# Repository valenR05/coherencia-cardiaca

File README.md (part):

<?xml version="1.0" encoding="utf-8"?>
<!DOCTYPE eagle SYSTEM "eagle.dtd">
<eagle version="9.6.2">
<drawing>
<settings>
<setting alwaysvectorfont="no"/>
<setting verticaltext="up"/>
</settings>
<grid distance="0.1" unitdist="inch" unit="inch" style="lines" multiple="1" display="no" altdistance="0.01" altunitdist="inch" altunit="inch"/>
<layers>
<layer number="1" name="Top" color="4" fill="1" visible="no" active="no"/>
<layer number="2" name="Route2" color="16" fill="1" visible="no" active="no"/>
<layer number="3" name="Route3" color="17" fill="1" visible="no" active="no"/>
<layer number="4" name="Route4" color="18" fill="1" visible="no" active="no"/>
<layer number="5" name="Route5" color="19" fill="1" visible="no" active="no"/>
<layer number="6" name="Route6" color="25" fill="1" visible="no" active="no"/>
<layer number="7" name="Route7" color="26" fill="1" visible="no" active="no"/>
<layer number="8" name="Route8" color="27" fill="1" visible="no" active="no"/>
<layer number="9" name="Route9" color="28" fill="1" visible="no" active="no"/>
<layer number="10" name="Route10" color="29" fill="1" visible="no" active="no"/>
<layer number="11" name="Route11" color="30" fill="1" visible="no" active="no"/>
<layer number="12" name="Route12" color="20" fill="1" visible="no" active="no"/>
<layer number="13" name="Route13" color="21" fill="1" visible="no" active="no"/>
<layer number="14" name="Route14" color="22" fill="1" visible="no" active="no"/>
<layer number="15" name="Route15" color="23" fill="1" visible="no" active="no"/>
<layer number="16" name="Bottom" color="1" fill="1" visible="no" active="no"/>
<layer number="17" name="Pads" color="2" fill="1" visible="no" active="no"/>
<layer number="18" name="Vias" color="2" fill="1" visible="no" active="no"/>
<layer number="19" name="Unrouted" color="6" fill="1" visible="no" active="no"/>
<layer number="20" name="Dimension" color="15" fill="1" visible="no" active="no"/>
<layer number="21" name="tPlace" color="7" fill="1" visible="no" active="no"/>
<layer number="22" name="bPlace" color="7" fill="1" visible="no" active="no"/>
<layer number="23" name="tOrigins" color="15" fill="1" visible="no" active="no"/>
<layer number="24" name="bOrigins" color="15" fill="1" visible="no" active="no"/>
<layer number="25" name="tNames" color="7" fill="1" visible="no" active="no"/>
<layer number="26" name="bNames" color="7" fill="1" visible="no" active="no"/>
<layer number="27" name="tValues" color="7" fill="1" visible="no" active="no"/>
<layer number="28" name="bValues" color="7" fill="1" visible="no" active="no"/>
<layer number="29" name="tStop" color="7" fill="3" visible="no" active="no"/>
<layer number="30" name="bStop" color="7" fill="6" visible="no" active="no"/>
<layer number="31" name="tCream" color="7" fill="4" visible="no" active="no"/>
<layer number="32" name="bCream" color="7" fill="5" visible="no" active="no"/>
<layer number="33" name="tFinish" color="6" fill="3" visible="no" active="no"/>
<layer number="34" name="bFinish" color="6" fill="6" visible="no" active="no"/>
<layer number="35" name="tGlue" color="7" fill="4" visible="no" active="no"/>
<layer number="36" name="bGlue" color="7" fill="5" visible="no" active="no"/>
<layer number="37" name="tTest" color="7" fill="1" visible="no" active="no"/>
<layer number="38" name="bTest" color="7" fill="1" visible="no" active="no"/>
<layer number="39" name="tKeepout" color="4" fill="11" visible="no" active="no"/>
<layer number="40" name="bKeepout" color="1" fill="11" visible="no" active="no"/>
<layer number="41" name="tRestrict" color="4" fill="10" visible="no" active="no"/>
<layer number="42" name="bRestrict" color="1" fill="10" visible="no" active="no"/>
<layer number="43" name="vRestrict" color="2" fill="10" visible="no" active="no"/>
<layer number="44" name="Drills" color="7" fill="1" visible="no" active="no"/>
<layer number="45" name="Holes" color="7" fill="1" visible="no" active="no"/>
<layer number="46" name="Milling" color="3" fill="1" visible="no" active="no"/>
<layer number="47" name="Measures" color="7" fill="1" visible="no" active="no"/>
<layer number="48" name="Document" color="7" fill="1" visible="no" active="no"/>
<layer number="49" name="Reference" color="7" fill="1" visible="no" active="no"/>
<layer number="50" name="dxf" color="7" fill="1" visible="no" active="no"/>
<layer number="51" name="tDocu" color="7" fill="1" visible="no" active="no"/>
<layer number="52" name="bDocu" color="7" fill="1" visible="no" active="no"/>
<layer number="53" name="tGND_GNDA" color="7" fill="9" visible="no" active="no"/>
<layer number="54" name="bGND_GNDA" color="1" fill="9" visible="no" active="no"/>
<layer number="56" name="wert" color="7" fill="1" visible="no" active="no"/>
<layer number="57" name="tCAD" color="7" fill="1" visible="no" active="no"/>
<layer number="59" name="tCarbon" color="7" fill="1" visible="no" active="no"/>
<layer number="60" name="bCarbon" color="7" fill="1" visible="no" active="no"/>
<layer number="88" name="SimResults" color="9" fill="1" visible="yes" active="yes"/>
<layer number="89" name="SimProbes" color="9" fill="1" visible="yes" active="yes"/>
<layer number="90" name="Modules" color="5" fill="1" visible="yes" active="yes"/>
<layer number="91" name="Nets" color="2" fill="1" visible="yes" active="yes"/>
<layer number="92" name="Busses" color="1" fill="1" visible="yes" active="yes"/>
<layer number="93" name="Pins" color="2" fill="1" visible="no" active="yes"/>
<layer number="94" name="Symbols" color="4" fill="1" visible="yes" active="yes"/>
<layer number="95" name="Names" color="7" fill="1" visible="yes" active="yes"/>
<layer number="96" name="Values" color="7" fill="1" visible="yes" active="yes"/>
<layer number="97" name="Info" color="7" fill="1" visible="yes" active="yes"/>
<layer number="98" name="Guide" color="6" fill="1" visible="yes" active="yes"/>
<layer number="99" name="SpiceOrder" color="7" fill="1" visible="no" active="no"/>
<layer number="100" name="Muster" color="7" fill="1" visible="no" active="no"/>
<layer number="101" name="Patch_Top" color="12" fill="4" visible="no" active="yes"/>
<layer number="102" name="Vscore" color="7" fill="1" visible="no" active="yes"/>
<layer number="103" name="fp3" color="7" fill="1" visible="no" active="yes"/>
<layer number="104" name="Name" color="7" fill="1" visible="no" active="yes"/>
<layer number="105" name="Beschreib" color="9" fill="1" visible="no" active="yes"/>
<layer number="106" name="BGA-Top" color="4" fill="1" visible="no" active="yes"/>
<layer number="107" name="BD-Top" color="5" fill="1" visible="no" active="yes"/>
<layer number="108" name="fp8" color="7" fill="1" visible="no" active="yes"/>
<layer number="109" name="fp9" color="7" fill="1" visible="no" active="yes"/>
<layer number="110" name="fp0" color="7" fill="1" visible="no" active="yes"/>
<layer number="111" name="LPC17xx" color="7" fill="1" visible="no" active="yes"/>
<layer number="112" name="tSilk" color="7" fill="1" visible="no" active="yes"/>
<layer number="113" name="ReferenceLS" color="7" fill="1" visible="no" active="no"/>
<layer number="116" name="Patch_BOT" color="9" fill="4" visible="no" active="yes"/>
<layer number="118" name="Rect_Pads" color="7" fill="1" visible="no" active="no"/>
<layer number="121" name="_tsilk" color="7" fill="1" visible="no" active="yes"/>
<layer number="122" name="_bsilk" color="7" fill="1" visible="no" active="yes"/>
<layer number="123" name="tTestmark" color="7" fill="1" visible="no" active="yes"/>
<layer number="124" name="bTestmark" color="7" fill="1" visible="no" active="yes"/>
<layer number="125" name="_tNames" color="7" fill="1" visible="no" active="yes"/>
<layer number="126" name="_bNames" color="7" fill="1" visible="no" active="yes"/>
<layer number="127" name="_tValues" color="7" fill="1" visible="no" active="yes"/>
<layer number="128" name="_bValues" color="7" fill="1" visible="no" active="yes"/>
<layer number="129" name="Mask" color="7" fill="1" visible="yes" active="yes"/>
<layer number="131" name="tAdjust" color="7" fill="1" visible="no" active="yes"/>
<layer number="132" name="bAdjust" color="7" fill="1" visible="no" active="yes"/>
<layer number="144" name="Drill_legend" color="7" fill="1" visible="no" active="yes"/>
<layer number="150" name="Notes" color="7" fill="1" visible="no" active="yes"/>
<layer number="151" name="HeatSink" color="7" fill="1" visible="no" active="yes"/>
<layer number="152" name="_bDocu" color="7" fill="1" visible="no" active="yes"/>
<layer number="153" name="FabDoc1" color="6" fill="1" visible="no" active="no"/>
<layer number="154" name="FabDoc2" color="2" fill="1" visible="no" active="no"/>
<layer number="155" name="FabDoc3" color="7" fill="15" visible="no" active="no"/>
<layer number="199" name="Contour" color="7" fill="1" visible="no" active="yes"/>
<layer number="200" name="200bmp" color="1" fill="10" visible="no" active="yes"/>
<layer number="201" name="201bmp" color="2" fill="1" visible="no" active="no"/>
<layer number="202" name="202bmp" color="3" fill="1" visible="no" active="no"/>
<layer number="203" name="203bmp" color="4" fill="10" visible="no" active="yes"/>
<layer number="204" name="204bmp" color="5" fill="10" visible="no" active="yes"/>
<layer number="205" name="205bmp" color="6" fill="10" visible="no" active="yes"/>
<layer number="206" name="206bmp" color="7" fill="10" visible="no" active="yes"/>
<layer number="207" name="207bmp" color="8" fill="10" visible="no" active="yes"/>
<layer number="208" name="208bmp" color="9" fill="10" visible="no" active="yes"/>
<layer number="209" name="209bmp" color="7" fill="1" visible="no" active="yes"/>
<layer number="210" name="210bmp" color="7" fill="1" visible="no" active="yes"/>
<layer number="211" name="211bmp" color="7" fill="1" visible="no" active="yes"/>
<layer number="212" name="212bmp" color="7" fill="1" visible="no" active="yes"/>
<layer number="213" name="213bmp" color="7" fill="1" visible="no" active="yes"/>
<layer number="214" name="214bmp" color="7" fill="1" visible="no" active="yes"/>
<layer number="215" name="215bmp" color="7" fill="1" visible="no" active="yes"/>
<layer number="216" name="216bmp" color="7" fill="1" visible="no" active="yes"/>
<layer number="217" name="217bmp" color="18" fill="1" visible="no" active="no"/>
<layer number="218" name="218bmp" color="19" fill="1" visible="no" active="no"/>
<layer number="219" name="219bmp" color="20" fill="1" visible="no" active="no"/>
<layer number="220" name="220bmp" color="21" fill="1" visible="no" active="no"/>
<layer number="221" name="221bmp" color="22" fill="1" visible="no" active="no"/>
<layer number="222" name="222bmp" color="23" fill="1" visible="no" active="no"/>
<layer number="223" name="223bmp" color="24" fill="1" visible="no" active="no"/>
<layer number="224" name="224bmp" color="25" fill="1" visible="no" active="no"/>
<layer number="225" name="225bmp" color="7" fill="1" visible="yes" active="yes"/>
<layer number="226" name="226bmp" color="7" fill="1" visible="yes" active="yes"/>
<layer number="227" name="227bmp" color="7" fill="1" visible="yes" active="yes"/>
<layer number="228" name="228bmp" color="7" fill="1" visible="yes" active="yes"/>
<layer number="229" name="229bmp" color="7" fill="1" visible="yes" active="yes"/>
<layer number="230" name="230bmp" color="7" fill="1" visible="yes" active="yes"/>
<layer number="231" name="Eagle3D_PG1" color="7" fill="1" visible="no" active="no"/>
<layer number="232" name="Eagle3D_PG2" color="7" fill="1" visible="no" active="no"/>
<layer number="233" name="Eagle3D_PG3" color="7" fill="1" visible="no" active="no"/>
<layer number="248" name="Housing" color="7" fill="1" visible="no" active="yes"/>
<layer number="249" name="Edge" color="7" fill="1" visible="no" active="yes"/>
<layer number="250" name="Descript" color="7" fill="1" visible="no" active="no"/>
<layer number="251" name="SMDround" color="7" fill="1" visible="no" active="no"/>
<layer number="254" name="cooling" color="7" fill="1" visible="no" active="yes"/>
<layer number="255" name="routoute" color="7" fill="1" visible="yes" active="yes"/>
</layers>
<schematic xreflabel="%F%N/%S.%C%R" xrefpart="/%S.%C%R">
<libraries>
<library name="TS321IDBVR">
<description>&lt;Texas Instruments TS321IDBVR Op Amp, 0.8MHz, 5  32 V, 5-Pin SOT-23&lt;/b&gt;&lt;p&gt;
&lt;author&gt;Created by SamacSys&lt;/author&gt;</description>
<packages>
<package name="SOT95P280X145-5N">
<description>&lt;b&gt;DBV0005A&lt;/b&gt;&lt;br&gt;
</description>
<smd name="1" x="-1.25" y="0.95" dx="1.2" dy="0.6" layer="1"/>
<smd name="2" x="-1.25" y="0" dx="1.2" dy="0.6" layer="1"/>
<smd name="3" x="-1.25" y="-0.95" dx="1.2" dy="0.6" layer="1"/>
<smd name="4" x="1.25" y="-0.95" dx="1.2" dy="0.6" layer="1"/>
<smd name="5" x="1.25" y="0.95" dx="1.2" dy="0.6" layer="1"/>
<text x="0" y="0" size="1.27" layer="25" align="center">&gt;NAME</text>
<text x="0" y="0" size="1.27" layer="27" align="center">&gt;VALUE</text>
<wire x1="-2.1" y1="1.775" x2="2.1" y2="1.775" width="0.05" layer="51"/>
<wire x1="2.1" y1="1.775" x2="2.1" y2="-1.775" width="0.05" layer="51"/>
<wire x1="2.1" y1="-1.775" x2="-2.1" y2="-1.775" width="0.05" layer="51"/>
<wire x1="-2.1" y1="-1.775" x2="-2.1" y2="1.775" width="0.05" layer="51"/>
<wire x1="-0.8" y1="1.45" x2="0.8" y2="1.45" width="0.1" layer="51"/>
<wire x1="0.8" y1="1.45" x2="0.8" y2="-1.45" width="0.1" layer="51"/>
<wire x1="0.8" y1="-1.45" x2="-0.8" y2="-1.45" width="0.1" layer="51"/>
<wire x1="-0.8" y1="-1.45" x2="-0.8" y2="1.45" width="0.1" layer="51"/>
<wire x1="-0.8" y1="0.5" x2="0.15" y2="1.45" width="0.1" layer="51"/>
<wire x1="-0.3" y1="1.45" x2="0.3" y2="1.45" width="0.2" layer="21"/>
<wire x1="0.3" y1="1.45" x2="0.3" y2="-1.45" width="0.2" layer="21"/>
<wire x1="0.3" y1="-1.45" x2="-0.3" y2="-1.45" width="0.2" layer="21"/>
<wire x1="-0.3" y1="-1.45" x2="-0.3" y2="1.45" width="0.2" layer="21"/>
<wire x1="-1.85" y1="1.5" x2="-0.65" y2="1.5" width="0.2" layer="21"/>
</package>
</packages>
<symbols>
<symbol name="TS321IDBVR">
<wire x1="5.08" y1="2.54" x2="22.86" y2="2.54" width="0.254" layer="94"/>
<wire x1="22.86" y1="-7.62" x2="22.86" y2="2.54" width="0.254" layer="94"/>
<wire x1="22.86" y1="-7.62" x2="5.08" y2="-7.62" width="0.254" layer="94"/>
<wire x1="5.08" y1="2.54" x2="5.08" y2="-7.62" width="0.254" layer="94"/>
<text x="24.13" y="7.62" size="1.778" layer="95" align="center-left">&gt;NAME</text>
<text x="24.13" y="5.08" size="1.778" layer="96" align="center-left">&gt;VALUE</text>
<pin name="OUT" x="0" y="0" length="middle"/>
<pin name="VCC" x="0" y="-2.54" length="middle"/>
<pin name="IN+" x="0" y="-5.08" length="middle"/>
<pin name="IN-" x="27.94" y="0" length="middle" rot="R180"/>
<pin name="VCC+" x="27.94" y="-2.54" length="middle" rot="R180"/>
</symbol>
</symbols>
<devicesets>
<deviceset name="TS321IDBVR" prefix="IC">
<description>&lt;b&gt;Texas Instruments TS321IDBVR Op Amp, 0.8MHz, 5  32 V, 5-Pin SOT-23&lt;/b&gt;&lt;p&gt;
Source: &lt;a href="http://www.ti.com/lit/gpn/ts321"&gt; Datasheet &lt;/a&gt;</description>
<gates>
<gate name="G$1" symbol="TS321IDBVR" x="0" y="0"/>
</gates>
<devices>
<device name="" package="SOT95P280X145-5N">
<connects>
<connect gate="G$1" pin="IN+" pad="3"/>
<connect gate="G$1" pin="IN-" pad="4"/>
<connect gate="G$1" pin="OUT" pad="1"/>
<connect gate="G$1" pin="VCC" pad="2"/>
<connect gate="G$1" pin="VCC+" pad="5"/>
</connects>
<technologies>
<technology name="">
<attribute name="DESCRIPTION" value="Texas Instruments TS321IDBVR Op Amp, 0.8MHz, 5  32 V, 5-Pin SOT-23" constant="no"/>
<attribute name="HEIGHT" value="1.45mm" constant="no"/>
<attribute name="MANUFACTURER_NAME" value="Texas Instruments" constant="no"/>
<attribute name="MANUFACTURER_PART_NUMBER" value="TS321IDBVR" constant="no"/>
<attribute name="MOUSER_PART_NUMBER" value="595-TS321IDBVR" constant="no"/>
<attribute name="MOUSER_PRICE-STOCK" value="https://www.mouser.co.uk/ProductDetail/Texas-Instruments/TS321IDBVR?qs=BBezV1N05%2FuyNsgiemJ6Dw%3D%3D" constant="no"/>
</technology>
</technologies>
</device>
</devices>
</deviceset>
</devicesets>
</library>
<library name="ESP32-S3-WROOM-1-N16R8">
<description>&lt;Multiprotocol Modules SMD Module, ESP32-S3R8, 3.3V, 8 MB Octal PSRAM Die, 16 MB Quad SPI Flash, PCB Antenna&lt;/b&gt;&lt;p&gt;
&lt;author&gt;Created by SamacSys&lt;/author&gt;</description>
<packages>
<package name="ESP32S3WROOM1N16R8">
<description>&lt;b&gt;ESP32-S3-WROOM-1-N16R8-5&lt;/b&gt;&lt;br&gt;
</description>
<smd name="1" x="-8.75" y="5.26" dx="1.5" dy="0.9" layer="1"/>
<smd name="2" x="-8.75" y="3.99" dx="1.5" dy="0.9" layer="1"/>
<smd name="3" x="-8.75" y="2.72" dx="1.5" dy="0.9" layer="1"/>
<smd name="4" x="-8.75" y="1.45" dx="1.5" dy="0.9" layer="1"/>
<smd name="5" x="-8.75" y="0.18" dx="1.5" dy="0.9" layer="1"/>
<smd name="6" x="-8.75" y="-1.09" dx="1.5" dy="0.9" layer="1"/>
<smd name="7" x="-8.75" y="-2.36" dx="1.5" dy="0.9" layer="1"/>
<smd name="8" x="-8.75" y="-3.63" dx="1.5" dy="0.9" layer="1"/>
<smd name="9" x="-8.75" y="-4.9" dx="1.5" dy="0.9" layer="1"/>
<smd name="10" x="-8.75" y="-6.17" dx="1.5" dy="0.9" layer="1"/>
<smd name="11" x="-8.75" y="-7.44" dx="1.5" dy="0.9" layer="1"/>
<smd name="12" x="-8.75" y="-8.71" dx="1.5" dy="0.9" layer="1"/>
<smd name="13" x="-8.75" y="-9.98" dx="1.5" dy="0.9" layer="1"/>
<smd name="14" x="-8.75" y="-11.25" dx="1.5" dy="0.9" layer="1"/>
<smd name="15" x="-6.985" y="-12.5" dx="1.5" dy="0.9" layer="1" rot="R90"/>
<smd name="16" x="-5.715" y="-12.5" dx="1.5" dy="0.9" layer="1" rot="R90"/>
<smd name="17" x="-4.445" y="-12.5" dx="1.5" dy="0.9" layer="1" rot="R90"/>
<smd name="18" x="-3.175" y="-12.5" dx="1.5" dy="0.9" layer="1" rot="R90"/>
<smd name="19" x="-1.905" y="-12.5" dx="1.5" dy="0.9" layer="1" rot="R90"/>
<smd name="20" x="-0.635" y="-12.5" dx="1.5" dy="0.9" layer="1" rot="R90"/>
<smd name="21" x="0.635" y="-12.5" dx="1.5" dy="0.9" layer="1" rot="R90"/>
<smd name="22" x="1.905" y="-12.5" dx="1.5" dy="0.9" layer="1" rot="R90"/>
<smd name="23" x="3.175" y="-12.5" dx="1.5" dy="0.9" layer="1" rot="R90"/>
<smd name="24" x="4.445" y="-12.5" dx="1.5" dy="0.9" layer="1" rot="R90"/>
<smd name="25" x="5.715" y="-12.5" dx="1.5" dy="0.9" layer="1" rot="R90"/>
<smd name="26" x="6.985" y="-12.5" dx="1.5" dy="0.9" layer="1" rot="R90"/>
<smd name="27" x="8.75" y="-11.25" dx="1.5" dy="0.9" layer="1"/>
<smd name="28" x="8.75" y="-9.98" dx="1.5" dy="0.9" layer="1"/>
<smd name="29" x="8.75" y="-8.71" dx="1.5" dy="0.9" layer="1"/>
<smd name="30" x="8.75" y="-7.44" dx="1.5" dy="0.9" layer="1"/>
<smd name="31" x="8.75" y="-6.17" dx="1.5" dy="0.9" layer="1"/>
<smd name="32" x="8.75" y="-4.9" dx="1.5" dy="0.9" layer="1"/>
<smd name="33" x="8.75" y="-3.63" dx="1.5" dy="0.9" layer="1"/>
<smd name="34" x="8.75" y="-2.36" dx="1.5" dy="0.9" layer="1"/>
<smd name="35" x="8.75" y="-1.09" dx="1.5" dy="0.9" layer="1"/>
<smd name="36" x="8.75" y="0.18" dx="1.5" dy="0.9" layer="1"/>
<smd name="37" x="8.75" y="1.45" dx="1.5" dy="0.9" layer="1"/>
<smd name="38" x="8.75" y="2.72" dx="1.5" dy="0.9" layer="1"/>
<smd name="39" x="8.75" y="3.99" dx="1.5" dy="0.9" layer="1"/>
<smd name="40" x="8.75" y="5.26" dx="1.5" dy="0.9" layer="1"/>
<smd name="41" x="-1.5" y="-2.46" dx="0.9" dy="0.9" layer="1" rot="R90"/>
<smd name="42" x="-2.9" y="-1.06" dx="0.9" dy="0.9" layer="1" rot="R90"/>
<smd name="43" x="-2.9" y="-2.46" dx="0.9" dy="0.9" layer="1" rot="R90"/>
<smd name="44" x="-2.9" y="-3.86" dx="0.9" dy="0.9" layer="1" rot="R90"/>
<smd name="45" x="-1.5" y="-3.86" dx="0.9" dy="0.9" layer="1" rot="R90"/>
<smd name="46" x="-0.1" y="-3.86" dx="0.9" dy="0.9" layer="1" rot="R90"/>
<smd name="47" x="-0.1" y="-2.46" dx="0.9" dy="0.9" layer="1" rot="R90"/>
<smd name="48" x="-0.1" y="-1.06" dx="0.9" dy="0.9" layer="1" rot="R90"/>
<smd name="49" x="-1.5" y="-1.06" dx="0.9" dy="0.9" layer="1" rot="R90"/>
<text x="0" y="-0.25" size="1.27" layer="25" align="center">&gt;NAME</text>
<text x="0" y="-0.25" size="1.27" layer="27" align="center">&gt;VALUE</text>
<wire x1="-9" y1="12.75" x2="9" y2="12.75" width="0.1" layer="51"/>
<wire x1="9" y1="12.75" x2="9" y2="-12.75" width="0.1" layer="51"/>
<wire x1="9" y1="-12.75" x2="-9" y2="-12.75" width="0.1" layer="51"/>
<wire x1="-9" y1="-12.75" x2="-9" y2="12.75" width="0.1" layer="51"/>
<wire x1="-10.5" y1="13.75" x2="10.5" y2="13.75" width="0.1" layer="51"/>
<wire x1="10.5" y1="13.75" x2="10.5" y2="-14.25" width="0.1" layer="51"/>
<wire x1="10.5" y1="-14.25" x2="-10.5" y2="-14.25" width="0.1" layer="51"/>
<wire x1="-10.5" y1="-14.25" x2="-10.5" y2="13.75" width="0.1" layer="51"/>
<wire x1="-9.9" y1="5.26" x2="-9.9" y2="5.26" width="0.1" layer="21"/>
<wire x1="-9.9" y1="5.26" x2="-10" y2="5.26" width="0.1" layer="21" curve="180"/>
<wire x1="-10" y1="5.26" x2="-10" y2="5.26" width="0.1" layer="21"/>
<wire x1="-10" y1="5.26" x2="-9.9" y2="5.26" width="0.1" layer="21" curve="180"/>
<wire x1="-9" y1="6" x2="-9" y2="12.75" width="0.2" layer="21"/>
<wire x1="-9" y1="12.75" x2="9" y2="12.75" width="0.2" layer="21"/>
<wire x1="9" y1="12.75" x2="9" y2="6" width="0.2" layer="21"/>
</package>
</packages>
<symbols>
<symbol name="ESP32-S3-WROOM-1-N16R8">
<wire x1="5.08" y1="2.54" x2="27.94" y2="2.54" width="0.254" layer="94"/>
<wire x1="27.94" y1="-63.5" x2="27.94" y2="2.54" width="0.254" layer="94"/>
<wire x1="27.94" y1="-63.5" x2="5.08" y2="-63.5" width="0.254" layer="94"/>
<wire x1="5.08" y1="2.54" x2="5.08" y2="-63.5" width="0.254" layer="94"/>
<text x="29.21" y="7.62" size="1.778" layer="95" align="center-left">&gt;NAME</text>
<text x="29.21" y="5.08" size="1.778" layer="96" align="center-left">&gt;VALUE</text>
<pin name="GND_1" x="0" y="0" length="middle"/>
<pin name="3V3" x="0" y="-2.54" length="middle"/>
<pin name="EN" x="0" y="-5.08" length="middle"/>
<pin name="IO4" x="0" y="-7.62" length="middle"/>
<pin name="IO5" x="0" y="-10.16" length="middle"/>
<pin name="IO6" x="0" y="-12.7" length="middle"/>
<pin name="IO7" x="0" y="-15.24" length="middle"/>
<pin name="IO15" x="0" y="-17.78" length="middle"/>
<pin name="IO16" x="0" y="-20.32" length="middle"/>
<pin name="IO17" x="0" y="-22.86" length="middle"/>
<pin name="IO18" x="0" y="-25.4" length="middle"/>
<pin name="IO8" x="0" y="-27.94" length="middle"/>
<pin name="IO19" x="0" y="-30.48" length="middle"/>
<pin name="IO20" x="0" y="-33.02" length="middle"/>
<pin name="IO3" x="0" y="-35.56" length="middle"/>
<pin name="IO46" x="0" y="-38.1" length="middle"/>
<pin name="IO9" x="0" y="-40.64" length="middle"/>
<pin name="IO10" x="0" y="-43.18" length="middle"/>
<pin name="IO11" x="0" y="-45.72" length="middle"/>
<pin name="IO12" x="0" y="-48.26" length="middle"/>
<pin name="IO13" x="0" y="-50.8" length="middle"/>
<pin name="IO14" x="0" y="-53.34" length="middle"/>
<pin name="IO21" x="0" y="-55.88" length="middle"/>
<pin name="IO47" x="0" y="-58.42" length="middle"/>
<pin name="IO48" x="0" y="-60.96" length="middle"/>
<pin name="IO45" x="33.02" y="0" length="middle" rot="R180"/>
<pin name="IO0" x="33.02" y="-2.54" length="middle" rot="R180"/>
<pin name="IO35" x="33.02" y="-5.08" length="middle" rot="R180"/>
<pin name="IO36" x="33.02" y="-7.62" length="middle" rot="R180"/>
<pin name="IO37" x="33.02" y="-10.16" length="middle" rot="R180"/>
<pin name="IO38" x="33.02" y="-12.7" length="middle" rot="R180"/>
<pin name="IO39" x="33.02" y="-15.24" length="middle" rot="R180"/>
<pin name="IO40" x="33.02" y="-17.78" length="middle" rot="R180"/>
<pin name="IO41" x="33.02" y="-20.32" length="middle" rot="R180"/>
<pin name="IO42" x="33.02" y="-22.86" length="middle" rot="R180"/>
<pin name="RXD0" x="33.02" y="-25.4" length="middle" rot="R180"/>
<pin name="TXD0" x="33.02" y="-27.94" length="middle" rot="R180"/>
<pin name="IO2" x="33.02" y="-30.48" length="middle" rot="R180"/>
<pin name="IO1" x="33.02" y="-33.02" length="middle" rot="R180"/>
<pin name="GND_2" x="33.02" y="-35.56" length="middle" rot="R180"/>
<pin name="GND_3" x="33.02" y="-38.1" length="middle" rot="R180"/>
<pin name="GND_4" x="33.02" y="-40.64" length="middle" rot="R180"/>
<pin name="GND_5" x="33.02" y="-43.18" length="middle" rot="R180"/>
<pin name="GND_6" x="33.02" y="-45.72" length="middle" rot="R180"/>
<pin name="GND_7" x="33.02" y="-48.26" length="middle" rot="R180"/>
<pin name="GND_8" x="33.02" y="-50.8" length="middle" rot="R180"/>
<pin name="GND_9" x="33.02" y="-53.34" length="middle" rot="R180"/>
<pin name="GND_10" x="33.02" y="-55.88" length="middle" rot="R180"/>
<pin name="GND_11" x="33.02" y="-58.42" length="middle" rot="R180"/>
</symbol>
</symbols>
<devicesets>
<deviceset name="ESP32-S3-WROOM-1-N16R8" prefix="IC">
<description>&lt;b&gt;Multiprotocol Modules SMD Module, ESP32-S3R8, 3.3V, 8 MB Octal PSRAM Die, 16 MB Quad SPI Flash, PCB Antenna&lt;/b&gt;&lt;p&gt;
Source: &lt;a href="https://www.espressif.com/sites/default/files/documentation/esp32-s3-wroom-1_wroom-1u_datasheet_en.pdf"&gt; Datasheet &lt;/a&gt;</description>
<gates>
<gate name="G$1" symbol="ESP32-S3-WROOM-1-N16R8" x="0" y="0"/>
</gates>
<devices>
<device name="" package="ESP32S3WROOM1N16R8">
<connects>
<connect gate="G$1" pin="3V3" pad="2"/>
<connect gate="G$1" pin="EN" pad="3"/>
<connect gate="G$1" pin="GND_1" pad="1"/>
<connect gate="G$1" pin="GND_10" pad="48"/>
<connect gate="G$1" pin="GND_11" pad="49"/>
<connect gate="G$1" pin="GND_2" pad="40"/>
<connect gate="G$1" pin="GND_3" pad="41"/>
<connect gate="G$1" pin="GND_4" pad="42"/>
<connect gate="G$1" pin="GND_5" pad="43"/>
<connect gate="G$1" pin="GND_6" pad="44"/>
<connect gate="G$1" pin="GND_7" pad="45"/>
<connect gate="G$1" pin="GND_8" pad="46"/>
<connect gate="G$1" pin="GND_9" pad="47"/>
<connect gate="G$1" pin="IO0" pad="27"/>
<connect gate="G$1" pin="IO1" pad="39"/>
<connect gate="G$1" pin="IO10" pad="18"/>
<connect gate="G$1" pin="IO11" pad="19"/>
<connect gate="G$1" pin="IO12" pad="20"/>
<connect gate="G$1" pin="IO13" pad="21"/>
<connect gate="G$1" pin="IO14" pad="22"/>
<connect gate="G$1" pin="IO15" pad="8"/>
<connect gate="G$1" pin="IO16" pad="9"/>
<connect gate="G$1" pin="IO17" pad="10"/>
<connect gate="G$1" pin="IO18" pad="11"/>
<connect gate="G$1" pin="IO19" pad="13"/>
<connect gate="G$1" pin="IO2" pad="38"/>
<connect gate="G$1" pin="IO20" pad="14"/>
<connect gate="G$1" pin="IO21" pad="23"/>
<connect gate="G$1" pin="IO3" pad="15"/>
<connect gate="G$1" pin="IO35" pad="28"/>
<connect gate="G$1" pin="IO36" pad="29"/>
<connect gate="G$1" pin="IO37" pad="30"/>
<connect gate="G$1" pin="IO38" pad="31"/>
<connect gate="G$1" pin="IO39" pad="32"/>
<connect gate="G$1" pin="IO4" pad="4"/>
<connect gate="G$1" pin="IO40" pad="33"/>
<connect gate="G$1" pin="IO41" pad="34"/>
<connect gate="G$1" pin="IO42" pad="35"/>
<connect gate="G$1" pin="IO45" pad="26"/>
<connect gate="G$1" pin="IO46" pad="16"/>
<connect gate="G$1" pin="IO47" pad="24"/>
<connect gate="G$1" pin="IO48" pad="25"/>
<connect gate="G$1" pin="IO5" pad="5"/>
<connect gate="G$1" pin="IO6" pad="6"/>
<connect gate="G$1" pin="IO7" pad="7"/>
<connect gate="G$1" pin="IO8" pad="12"/>
<connect gate="G$1" pin="IO9" pad="17"/>
<connect gate="G$1" pin="RXD0" pad="36"/>
<connect gate="G$1" pin="TXD0" pad="37"/>
</connects>
<technologies>
<technology name="">
<attribute name="DESCRIPTION" value="Multiprotocol Modules SMD Module, ESP32-S3R8, 3.3V, 8 MB Octal PSRAM Die, 16 MB Quad SPI Flash, PCB Antenna" constant="no"/>
<attribute name="HEIGHT" value="3.25mm" constant="no"/>
<attribute name="MANUFACTURER_NAME" value="Espressif Systems" constant="no"/>
<attribute name="MANUFACTURER_PART_NUMBER" value="ESP32-S3-WROOM-1-N16R8" constant="no"/>
<attribute name="MOUSER_PART_NUMBER" value="356-ESP32S3WRM1N16R8" constant="no"/>
<attribute name="MOUSER_PRICE-STOCK" value="https://www.mouser.co.uk/ProductDetail/Espressif-Systems/ESP32-S3-WROOM-1-N16R8?qs=Li%252BoUPsLEnvQc9gW6AMhZg%3D%3D" constant="no"/>
</technology>
</technologies>
</device>
</devices>
</deviceset>
</devicesets>
</library>
<library name="MAX30102EFD+T">
<description>&lt;Biometric Sensors Integrated Optical Sensor&lt;/b&gt;&lt;p&gt;
&lt;author&gt;Created by SamacSys&lt;/author&gt;</description>
<packages>
<package name="MAX30102EFDT">
<description>&lt;b&gt;F143A5MK+1&lt;/b&gt;&lt;br&gt;
</description>
<smd name="1" x="-1.2" y="2.4" dx="0.75" dy="0.35" layer="1"/>
<smd name="2" x="-1.2" y="1.6" dx="0.75" dy="0.35" layer="1"/>
<smd name="3" x="-1.2" y="0.8" dx="0.75" dy="0.35" layer="1"/>
<smd name="4" x="-1.2" y="0" dx="0.75" dy="0.35" layer="1"/>
<smd name="5" x="-1.2" y="-0.8" dx="0.75" dy="0.35" layer="1"/>
<smd name="6" x="-1.2" y="-1.6" dx="0.75" dy="0.35" layer="1"/>
<smd name="7" x="-1.2" y="-2.4" dx="0.75" dy="0.35" layer="1"/>
<smd name="8" x="1.2" y="-2.4" dx="0.75" dy="0.35" layer="1"/>
<smd name="9" x="1.2" y="-1.6" dx="0.75" dy="0.35" layer="1"/>
<smd name="10" x="1.2" y="-0.8" dx="0.75" dy="0.35" layer="1"/>
<smd name="11" x="1.2" y="0" dx="0.75" dy="0.35" layer="1"/>
<smd name="12" x="1.2" y="0.8" dx="0.75" dy="0.35" layer="1"/>
<smd name="13" x="1.2" y="1.6" dx="0.75" dy="0.35" layer="1"/>
<smd name="14" x="1.2" y="2.4" dx="0.75" dy="0.35" layer="1"/>
<text x="0" y="0" size="1.27" layer="25" align="center">&gt;NAME</text>
<text x="0" y="0" size="1.27" layer="27" align="center">&gt;VALUE</text>
<wire x1="-1.65" y1="2.8" x2="1.65" y2="2.8" width="0.1" layer="51"/>
<wire x1="1.65" y1="2.8" x2="1.65" y2="-2.8" width="0.1" layer="51"/>
<wire x1="1.65" y1="-2.8" x2="-1.65" y2="-2.8" width="0.1" layer="51"/>
<wire x1="-1.65" y1="-2.8" x2="-1.65" y2="2.8" width="0.1" layer="51"/>
<wire x1="-2.65" y1="3.8" x2="2.65" y2="3.8" width="0.1" layer="51"/>
<wire x1="2.65" y1="3.8" x2="2.65" y2="-3.8" width="0.1" layer="51"/>
<wire x1="2.65" y1="-3.8" x2="-2.65" y2="-3.8" width="0.1" layer="51"/>
<wire x1="-2.65" y1="-3.8" x2="-2.65" y2="3.8" width="0.1" layer="51"/>
<wire x1="-2.2" y1="2.4" x2="-2.2" y2="2.4" width="0.1" layer="21"/>
<wire x1="-2.2" y1="2.4" x2="-2.3" y2="2.4" width="0.1" layer="21" curve="180"/>
<wire x1="-2.3" y1="2.4" x2="-2.3" y2="2.4" width="0.1" layer="21"/>
<wire x1="-2.3" y1="2.4" x2="-2.2" y2="2.4" width="0.1" layer="21" curve="180"/>
</package>
</packages>
<symbols>
<symbol name="MAX30102EFD+T">
<wire x1="5.08" y1="2.54" x2="30.48" y2="2.54" width="0.254" layer="94"/>
<wire x1="30.48" y1="-17.78" x2="30.48" y2="2.54" width="0.254" layer="94"/>
<wire x1="30.48" y1="-17.78" x2="5.08" y2="-17.78" width="0.254" layer="94"/>
<wire x1="5.08" y1="2.54" x2="5.08" y2="-17.78" width="0.254" layer="94"/>
<text x="31.75" y="7.62" size="1.778" layer="95" align="center-left">&gt;NAME</text>
<text x="31.75" y="5.08" size="1.778" layer="96" align="center-left">&gt;VALUE</text>
<pin name="N.C._1" x="0" y="0" length="middle"/>
<pin name="SCL" x="0" y="-2.54" length="middle"/>
<pin name="SDA" x="0" y="-5.08" length="middle"/>
<pin name="PGND" x="0" y="-7.62" length="middle"/>
<pin name="N.C._2" x="0" y="-10.16" length="middle"/>
<pin name="N.C._3" x="0" y="-12.7" length="middle"/>
<pin name="N.C._4" x="0" y="-15.24" length="middle"/>
<pin name="N.C._5" x="35.56" y="-15.24" length="middle" rot="R180"/>
<pin name="VLED+_1" x="35.56" y="-12.7" length="middle" rot="R180"/>
<pin name="VLED+_2" x="35.56" y="-10.16" length="middle" rot="R180"/>
<pin name="VDD" x="35.56" y="-7.62" length="middle" rot="R180"/>
<pin name="GND" x="35.56" y="-5.08" length="middle" rot="R180"/>
<pin name="!INT" x="35.56" y="-2.54" length="middle" rot="R180"/>
<pin name="N.C._6" x="35.56" y="0" length="middle" rot="R180"/>
</symbol>
</symbols>
<devicesets>
<deviceset name="MAX30102EFD+T" prefix="IC">
<description>&lt;b&gt;Biometric Sensors Integrated Optical Sensor&lt;/b&gt;&lt;p&gt;
Source: &lt;a href="https://www.analog.com/media/en/technical-documentation/data-sheets/MAX30102.pdf"&gt; Datasheet &lt;/a&gt;</description>
<gates>
<gate name="G$1" symbol="MAX30102EFD+T" x="0" y="0"/>
</gates>
<devices>
<device name="" package="MAX30102EFDT">
<connects>
<connect gate="G$1" pin="!INT" pad="13"/>
<connect gate="G$1" pin="GND" pad="12"/>
<connect gate="G$1" pin="N.C._1" pad="1"/>
<connect gate="G$1" pin="N.C._2" pad="5"/>
<connect gate="G$1" pin="N.C._3" pad="6"/>
<connect gate="G$1" pin="N.C._4" pad="7"/>
<connect gate="G$1" pin="N.C._5" pad="8"/>
<connect gate="G$1" pin="N.C._6" pad="14"/>
<connect gate="G$1" pin="PGND" pad="4"/>
<connect gate="G$1" pin="SCL" pad="2"/>
<connect gate="G$1" pin="SDA" pad="3"/>
<connect gate="G$1" pin="VDD" pad="11"/>
<connect gate="G$1" pin="VLED+_1" pad="9"/>
<connect gate="G$1" pin="VLED+_2" pad="10"/>
</connects>
<technologies>
<technology name="">
<attribute name="DESCRIPTION" value="Biometric Sensors Integrated Optical Sensor" constant="no"/>
<attribute name="HEIGHT" value="1.65mm" constant="no"/>
<attribute name="MANUFACTURER_NAME" value="Analog Devices" constant="no"/>
<attribute name="MANUFACTURER_PART_NUMBER" value="MAX30102EFD+T" constant="no"/>
<attribute name="MOUSER_PART_NUMBER" value="700-MAX30102EFD+T" constant="no"/>
<attribute name="MOUSER_PRICE-STOCK" value="https://www.mouser.co.uk/ProductDetail/Analog-Devices-Maxim-Integrated/MAX30102EFD%2bT?qs=nVS1qgv%252BQrkHA4%2FoFYriFA%3D%3D" constant="no"/>
</technology>
</technologies>
</device>
</devices>
</deviceset>
</devicesets>
</library>
<library name="0805S8F1202P5E">
<description>&lt;Jumper Wires &amp; Zero-ohm Resistors&lt;/b&gt;&lt;p&gt;
&lt;author&gt;Created by SamacSys&lt;/author&gt;</description>
<packages>
<package name="RESC2013X65N">
<description>&lt;b&gt;0805&lt;/b&gt;&lt;br&gt;
</description>
<smd name="1" x="-0.95" y="0" dx="1.45" dy="1" layer="1" rot="R90"/>
<smd name="2" x="0.95" y="0" dx="1.45" dy="1" layer="1" rot="R90"/>
<text x="0" y="0" size="1.27" layer="25" align="center">&gt;NAME</text>
<text x="0" y="0" size="1.27" layer="27" align="center">&gt;VALUE</text>
<wire x1="-1.7" y1="1" x2="1.7" y2="1" width="0.05" layer="51"/>
<wire x1="1.7" y1="1" x2="1.7" y2="-1" width="0.05" layer="51"/>
<wire x1="1.7" y1="-1" x2="-1.7" y2="-1" width="0.05" layer="51"/>
<wire x1="-1.7" y1="-1" x2="-1.7" y2="1" width="0.05" layer="51"/>
<wire x1="-1" y1="0.638" x2="1" y2="0.638" width="0.1" layer="51"/>
<wire x1="1" y1="0.638" x2="1" y2="-0.638" width="0.1" layer="51"/>
<wire x1="1" y1="-0.638" x2="-1" y2="-0.638" width="0.1" layer="51"/>
<wire x1="-1" y1="-0.638" x2="-1" y2="0.638" width="0.1" layer="51"/>
<wire x1="0" y1="0.538" x2="0" y2="-0.538" width="0.2" layer="21"/>
</package>
</packages>
<symbols>
<symbol name="0805S8F1202P5E">
<wire x1="5.08" y1="1.27" x2="12.7" y2="1.27" width="0.254" layer="94"/>
<wire x1="12.7" y1="-1.27" x2="12.7" y2="1.27" width="0.254" layer="94"/>
<wire x1="12.7" y1="-1.27" x2="5.08" y2="-1.27" width="0.254" layer="94"/>
<wire x1="5.08" y1="1.27" x2="5.08" y2="-1.27" width="0.254" layer="94"/>
<text x="13.97" y="6.35" size="1.778" layer="95" align="center-left">&gt;NAME</text>
<text x="13.97" y="3.81" size="1.778" layer="96" align="center-left">&gt;VALUE</text>
<pin name="1" x="0" y="0" visible="pad" length="middle"/>
<pin name="2" x="17.78" y="0" visible="pad" length="middle" rot="R180"/>
</symbol>
</symbols>
<devicesets>
<deviceset name="0805S8F1202P5E" prefix="R">
<description>&lt;b&gt;Jumper Wires &amp; Zero-ohm Resistors&lt;/b&gt;&lt;p&gt;
Source: &lt;a href="https://co.mouser.com/datasheet/3/5925/1/1.pdf"&gt; Datasheet &lt;/a&gt;</description>
<gates>
<gate name="G$1" symbol="0805S8F1202P5E" x="0" y="0"/>
</gates>
<devices>
<device name="" package="RESC2013X65N">
<connects>
<connect gate="G$1" pin="1" pad="1"/>
<connect gate="G$1" pin="2" pad="2"/>
</connects>
<technologies>
<technology name="">
<attribute name="ARROW_PART_NUMBER" value="" constant="no"/>
<attribute name="ARROW_PRICE-STOCK" value="" constant="no"/>
<attribute name="DESCRIPTION" value="Jumper Wires &amp; Zero-ohm Resistors" constant="no"/>
<attribute name="HEIGHT" value="0.65mm" constant="no"/>
<attribute name="MANUFACTURER_NAME" value="ROYALOHM" constant="no"/>
<attribute name="MANUFACTURER_PART_NUMBER" value="0805S8F1202P5E" constant="no"/>
<attribute name="MOUSER_PART_NUMBER" value="" constant="no"/>
<attribute name="MOUSER_PRICE-STOCK" value="" constant="no"/>
</technology>
</technologies>
</device>
</devices>
</deviceset>
</devicesets>
</library>
<library name="C0805J104K1RACAUTO">
<description>&lt;SMD Auto X7R FO, Ceramic, 0.1 uF, 10%, 100 VDC, X7R, SMD, MLCC, Open Mode, Automotive Grade, 0805, 0.6 mm&lt;/b&gt;&lt;p&gt;
&lt;author&gt;Created by SamacSys&lt;/author&gt;</description>
<packages>
<package name="CAPC2012X140N">
<description>&lt;b&gt;C0805 (1.4)&lt;/b&gt;&lt;br&gt;
</description>
<smd name="1" x="-0.81" y="0" dx="1.57" dy="1.1" layer="1" rot="R90"/>
<smd name="2" x="0.81" y="0" dx="1.57" dy="1.1" layer="1" rot="R90"/>
<text x="0" y="0" size="1.27" layer="25" align="center">&gt;NAME</text>
<text x="0" y="0" size="1.27" layer="27" align="center">&gt;VALUE</text>
<wire x1="-1.51" y1="0.94" x2="1.51" y2="0.94" width="0.05" layer="51"/>
<wire x1="1.51" y1="0.94" x2="1.51" y2="-0.94" width="0.05" layer="51"/>
<wire x1="1.51" y1="-0.94" x2="-1.51" y2="-0.94" width="0.05" layer="51"/>
<wire x1="-1.51" y1="-0.94" x2="-1.51" y2="0.94" width="0.05" layer="51"/>
<wire x1="-1" y1="0.625" x2="1" y2="0.625" width="0.1" layer="51"/>
<wire x1="1" y1="0.625" x2="1" y2="-0.625" width="0.1" layer="51"/>
<wire x1="1" y1="-0.625" x2="-1" y2="-0.625" width="0.1" layer="51"/>
<wire x1="-1" y1="-0.625" x2="-1" y2="0.625" width="0.1" layer="51"/>
</package>
</packages>
<symbols>
<symbol name="C0805J104K1RACAUTO">
<wire x1="5.588" y1="2.54" x2="5.588" y2="-2.54" width="0.254" layer="94"/>
<wire x1="7.112" y1="2.54" x2="7.112" y2="-2.54" width="0.254" layer="94"/>
<wire x1="5.08" y1="0" x2="5.588" y2="0" width="0.254" layer="94"/>
<wire x1="7.112" y1="0" x2="7.62" y2="0" width="0.254" layer="94"/>
<text x="8.89" y="6.35" size="1.778" layer="95" align="center-left">&gt;NAME</text>
<text x="8.89" y="3.81" size="1.778" layer="96" align="center-left">&gt;VALUE</text>
<pin name="1" x="0" y="0" visible="pad" length="middle"/>
<pin name="2" x="12.7" y="0" visible="pad" length="middle" rot="R180"/>
</symbol>
</symbols>
<devicesets>
<deviceset name="C0805J104K1RACAUTO" prefix="C">
<description>&lt;b&gt;SMD Auto X7R FO, Ceramic, 0.1 uF, 10%, 100 VDC, X7R, SMD, MLCC, Open Mode, Automotive Grade, 0805, 0.6 mm&lt;/b&gt;&lt;p&gt;
Source: &lt;a href="https://search.kemet.com/component-documentation/download/specsheet/C0805J104K1RACAUTO"&gt; Datasheet &lt;/a&gt;</description>
<gates>
<gate name="G$1" symbol="C0805J104K1RACAUTO" x="0" y="0"/>
</gates>
<devices>
<device name="" package="CAPC2012X140N">
<connects>
<connect gate="G$1" pin="1" pad="1"/>
<connect gate="G$1" pin="2" pad="2"/>
</connects>
<technologies>
<technology name="">
<attribute name="DESCRIPTION" value="SMD Auto X7R FO, Ceramic, 0.1 uF, 10%, 100 VDC, X7R, SMD, MLCC, Open Mode, Automotive Grade, 0805, 0.6 mm" constant="no"/>
<attribute name="HEIGHT" value="1.4mm" constant="no"/>
<attribute name="MANUFACTURER_NAME" value="KEMET" constant="no"/>
<attribute name="MANUFACTURER_PART_NUMBER" value="C0805J104K1RACAUTO" constant="no"/>
<attribute name="MOUSER_PART_NUMBER" value="" constant="no"/>
<attribute name="MOUSER_PRICE-STOCK" value="" constant="no"/>
</technology>
</technologies>
</device>
</devices>
</deviceset>
</devicesets>
</library>
<library name="supply1" urn="urn:adsk.eagle:library:371">
<description>&lt;b&gt;Supply Symbols&lt;/b&gt;&lt;p&gt;
 GND, VCC, 0V, +5V, -5V, etc.&lt;p&gt;
 Please keep in mind, that these devices are necessary for the
 automatic wiring of the supply signals.&lt;p&gt;
 The pin name defined in the symbol is identical to the net which is to be wired automatically.&lt;p&gt;
 In this library the device names are the same as the pin names of the symbols, therefore the correct signal names appear next to the supply symbols in the schematic.&lt;p&gt;
 &lt;author&gt;Created by librarian@cadsoft.de&lt;/author&gt;</description>
<packages>
</packages>
<symbols>
<symbol name="+3V3" urn="urn:adsk.eagle:symbol:26950/1" library_version="1">
<wire x1="1.27" y1="-1.905" x2="0" y2="0" width="0.254" layer="94"/>
<wire x1="0" y1="0" x2="-1.27" y2="-1.905" width="0.254" layer="94"/>
<text x="-2.54" y="-5.08" size="1.778" layer="96" rot="R90">&gt;VALUE</text>
<pin name="+3V3" x="0" y="-2.54" visible="off" length="short" direction="sup" rot="R90"/>
</symbol>
<symbol name="GND" urn="urn:adsk.eagle:symbol:26925/1" library_version="1">
<wire x1="-1.905" y1="0" x2="1.905" y2="0" width="0.254" layer="94"/>
<text x="-2.54" y="-2.54" size="1.778" layer="96">&gt;VALUE</text>
<pin name="GND" x="0" y="2.54" visible="off" length="short" direction="sup" rot="R270"/>
</symbol>
</symbols>
<devicesets>
<deviceset name="+3V3" urn="urn:adsk.eagle:component:26981/1" prefix="+3V3" library_version="1">
<description>&lt;b&gt;SUPPLY SYMBOL&lt;/b&gt;</description>
<gates>
<gate name="G$1" symbol="+3V3" x="0" y="0"/>
</gates>
<devices>
<device name="">
<technologies>
<technology name=""/>
</technologies>
</device>
</devices>
</deviceset>
<deviceset name="GND" urn="urn:adsk.eagle:component:26954/1" prefix="GND" library_version="1">
<description>&lt;b&gt;SUPPLY SYMBOL&lt;/b&gt;</description>
<gates>
<gate name="1" symbol="GND" x="0" y="0"/>
</gates>
<devices>
<device name="">
<technologies>
<technology name=""/>
</technologies>
</device>
</devices>
</deviceset>
</devicesets>
</library>
<library name="frames" urn="urn:adsk.eagle:library:229">
<description>&lt;b&gt;Frames for Sheet and Layout&lt;/b&gt;</description>
<packages>
</packages>
<symbols>
<symbol name="A3L-LOC" urn="urn:adsk.eagle:symbol:13881/1" library_version="1">
<wire x1="288.29" y1="3.81" x2="342.265" y2="3.81" width="0.1016" layer="94"/>
<wire x1="342.265" y1="3.81" x2="373.38" y2="3.81" width="0.1016" layer="94"/>
<wire x1="373.38" y1="3.81" x2="383.54" y2="3.81" width="0.1016" layer="94"/>
<wire x1="383.54" y1="3.81" x2="383.54" y2="8.89" width="0.1016" layer="94"/>
<wire x1="383.54" y1="8.89" x2="383.54" y2="13.97" width="0.1016" layer="94"/>
<wire x1="383.54" y1="13.97" x2="383.54" y2="19.05" width="0.1016" layer="94"/>
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
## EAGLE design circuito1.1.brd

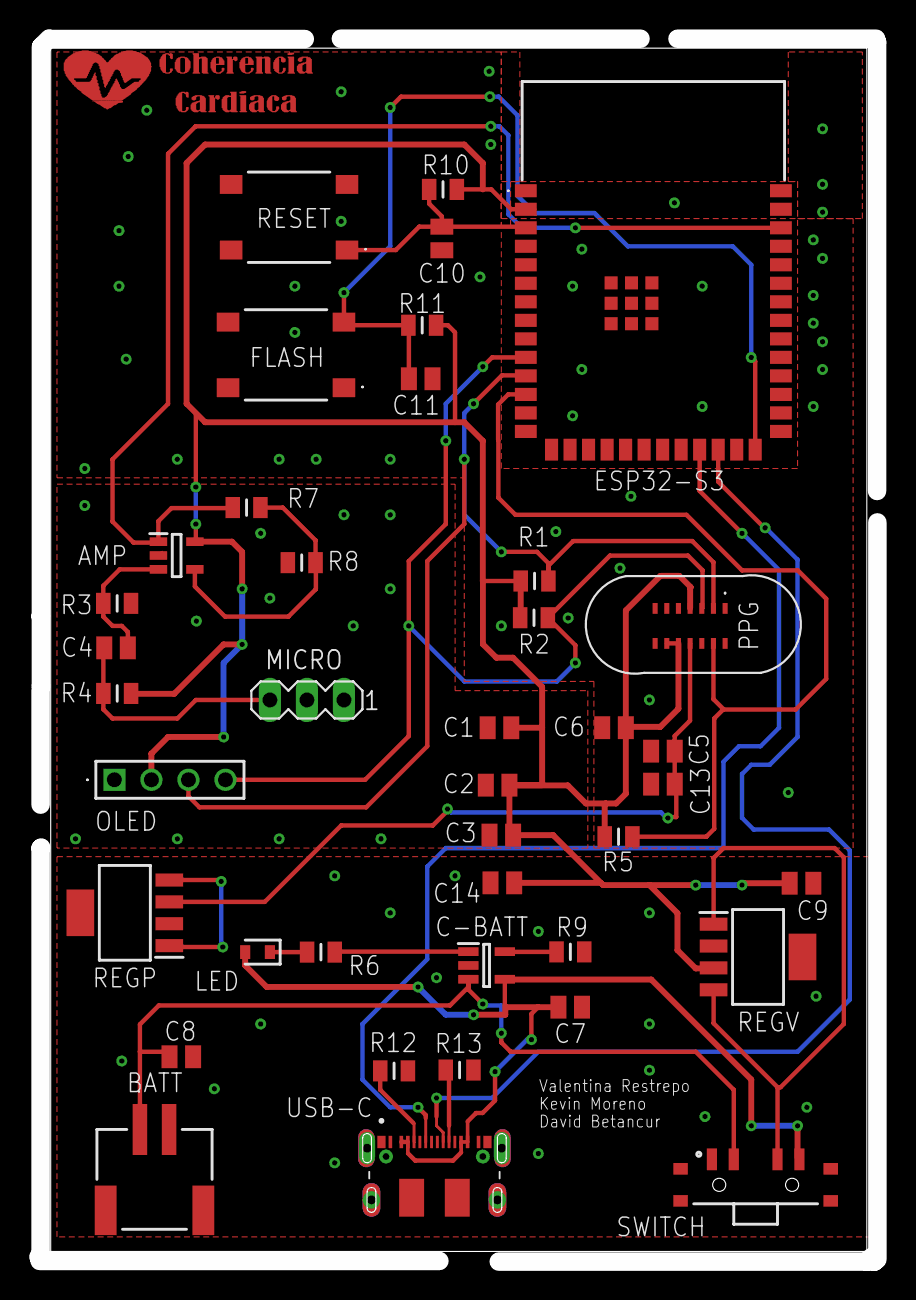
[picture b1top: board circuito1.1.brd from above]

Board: 2 copper layers, 57.5 x 83.9 mm, 40 parts (0 on the bottom side), 23 nets.

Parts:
AMP: TS321IDBVR; SOT95P280X145-5N
BATT: 1769
C1, C2, C5, C13: 100nF; CAPC2012X140N
C3, C6, C14: 10µF; CAPC2012X140N
C4: 0.1µF; CAPC2012X140N
C7, C8: 10U; CAPC2012X140N
C9, C10, C11: 0,1U; CAPC2012X140N
C-BATT: MCP73831T-2ACI_OT; SOT95P270X145-5N
ESP32-S3: ESP32-S3-WROOM-1-N16R8; ESP32S3WROOM1N16R8
FLASH: DTSM-61N-V-T_R; DTSM61NVTR
LED: SML-D12U8WT86C; LEDC1608X65N
MICRO: MA03-1
OLED: TSW-104-07-G-S; TSW10407GS
PPG: MAX30102EFD+T; MAX30102EFDT
R1, R2, R4: 4,7k; RESC2013X65N
R3, R5, R8, R10, R11: 10K; RESC2013X65N
R6, R12, R13: 5,1K; RESC2013X65N
R7: 200K; RESC2013X65N
R9: 2K; RESC2013X65N
REGP: LP38692MP-1.8_NOPB; SOT150P700X180-5N
REGV: LP38692MP-3.3_NOPB; SOT150P700X180-5N
RESET: DTSM-61N-V-T_R; DTSM61NVTR
SWITCH: PCM13SMTR; SW_PCM13SMTR
USB-C: CX90B-16P1; HIROSE_CX90B-16P1

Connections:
+3V3: AMP.5, C1.2, C2.2, C3.2, C6.2, C9.1, C14.2, ESP32-S3.2, OLED.2, PPG.4, PPG.9, PPG.10, R1.2, R2.1, R4.2, R5.2, R10.2, R11.2, REGV.3
BATT+: BATT.1, C8.1, C-BATT.3, SWITCH.2
COMM: REGP.1, REGP.4
D1+: ESP32-S3.23, USB-C.A6
D1-: ESP32-S3.24, USB-C.A7
EN: C10.1, ESP32-S3.3, R10.1, RESET.1
GND: AMP.2, BATT.2, C1.1, C2.1, C3.1, C5.1, C6.1, C7.1, C8.2, C9.2, C10.2, C11.1, C13.1, C14.1, C-BATT.2, ESP32-S3.1, ESP32-S3.40, ESP32-S3.41, ESP32-S3.42, ESP32-S3.43, ESP32-S3.44, ESP32-S3.45, ESP32-S3.46, ESP32-S3.47, ESP32-S3.48, ESP32-S3.49, FLASH.1, MICRO.2, OLED.1, PPG.12, R3.2, R8.1, R9.2, R12.1, R13.1, REGP.5, REGV.5, RESET.3, USB-C.A1, USB-C.A12, USB-C.B1, USB-C.B12
INT: ESP32-S3.12, PPG.13, R5.1
unnamed: AMP.3, C4.2, R3.1
unnamed: C-BATT.1, R6.1
unnamed: AMP.4, R7.2, R8.2
unnamed: LED.1, R6.2
unnamed: REGV.1, REGV.4, SWITCH.3
unnamed: R12.2, USB-C.A5
unnamed: R13.2, USB-C.B5
unnamed: C4.1, MICRO.3, R4.1
unnamed: C-BATT.5, R9.1
unnamed: C11.2, ESP32-S3.26, FLASH.3, R11.1
OUT: AMP.1, ESP32-S3.38, R7.1
SCL: ESP32-S3.11, OLED.3, PPG.2, R1.1
SDA: ESP32-S3.10, OLED.4, PPG.3, R2.2
VDD: C7.2, C-BATT.4, LED.2, SWITCH.4, USB-C.A4, USB-C.A9, USB-C.B4, USB-C.B9
VDD2: C5.2, C13.2, PPG.11, REGP.3

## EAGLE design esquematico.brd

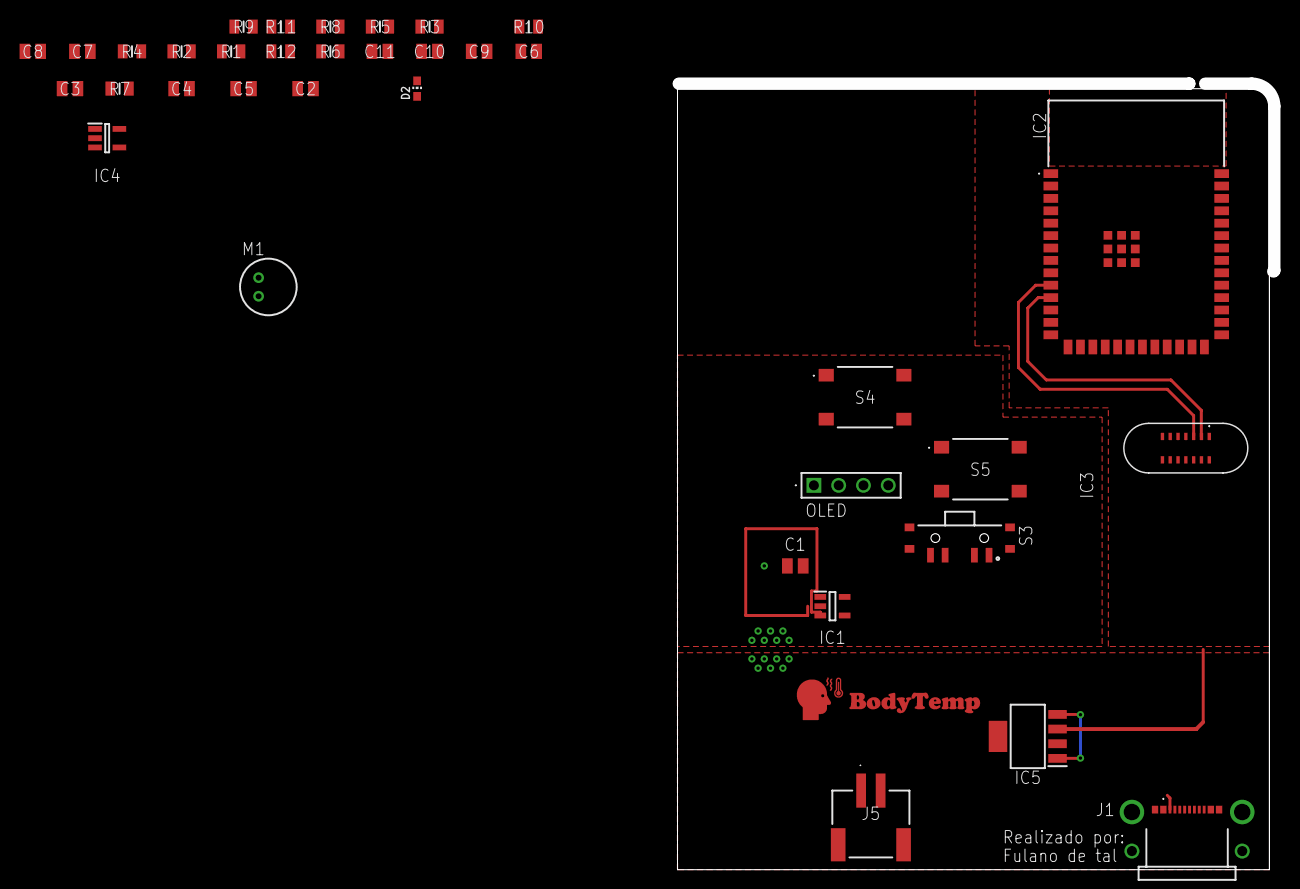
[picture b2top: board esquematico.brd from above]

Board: 2 copper layers, 61.1 x 80.5 mm, 36 parts (0 on the bottom side), 20 nets.

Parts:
C1, C2, C5: 100nF; CAPC2012X140N
C3, C6: 10µF; CAPC2012X140N
C4: 0.1µF; CAPC2012X140N
C7, C8: 10U; CAPC2012X140N
C9, C10, C11: 0,1U; CAPC2012X140N
D2: LED_CHIP-LED0603MP
IC1: TS321IDBVR; SOT95P280X145-5N
IC2: ESP32-S3-WROOM-1-N16R8; ESP32S3WROOM1N16R8
IC3: MAX30102EFD+T; MAX30102EFDT
IC4: MCP73831T-2ACI_OT; SOT95P270X145-5N
IC5: LP38692MP-3.3_NOPB; SOT150P700X180-5N
J1: UJ20-C-H-G-MSMT-P16-TR-67; UJ20CHGMSMTP16TR67
J5: 1769
M1: ELECTRET_MICROPHON-WM.64PN; WM-64PN
OLED: TSW-104-07-G-S; TSW10407GS
R1, R2, R4: 4,7k; RESC2013X65N
R3, R5, R8, R10, R11: 10K; RESC2013X65N
R6, R12: 5,1K; RESC2013X65N
R7: 200K; RESC2013X65N
R9: 2K; RESC2013X65N
S3: PCM13SMTR; SW_PCM13SMTR
S4, S5: DTSM-61N-V-T_R; DTSM61NVTR

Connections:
+3V3: C1.2, C3.2, C5.2, C6.2, C9.1, IC1.2, IC1.5, IC2.2, IC3.9, IC3.10, IC3.11, IC5.3, OLED.2, R1.2, R2.1, R4.2, R5.2, R10.2, R11.2
+5V: C7.2, D2.C, IC4.4, J1.A4, J1.B4, S3.4
DN1: IC2.9, J1.A7
DP1: IC2.8, J1.A6
GND: C1.1, C2.1, C3.1, C5.1, C6.1, C7.1, C8.2, C9.2, C10.2, C11.1, IC2.1, IC2.40, IC2.41, IC2.42, IC2.43, IC2.44, IC2.45, IC2.46, IC2.47, IC2.48, IC2.49, IC3.4, IC3.12, IC4.2, IC5.5, J1.A12, J1.S1, J1.S2, J1.S3, J1.S4, J5.2, M1.1, OLED.1, R3.2, R8.1, R9.2, R12.1, S4.3, S5.1
GND1: C11.2, IC2.26, R11.1, S5.3
INT: IC3.13, R5.1
INT1: C10.1, IC2.3, R10.1, S4.1
unnamed: C4.2, IC1.3, R3.1
unnamed: C4.1, M1.2, R4.1
unnamed: IC4.1, R6.1
unnamed: IC1.4, R7.2, R8.2
unnamed: D2.A, R6.2
unnamed: IC5.1, IC5.4, S3.3
unnamed: C8.1, J5.1
unnamed: J1.A5, R12.2
unnamed: IC4.5, R9.1
OUT: IC1.1, IC2.38, R7.1
SCL: IC2.11, IC3.2, OLED.3, R1.1
SDA: IC2.10, IC3.3, R2.2

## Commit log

2025-10-03 Se reorganizo el esquematico por bloques
2025-10-04 Finalizado Bloque 1: Acondicionador de señal
2025-10-05 Finalizado bloque 2: Sensor PPG (PulsiOximetro)
2025-10-10 Se corrigieron algunos bloques y se anoto lo faltante
2025-10-13 Create esquematico.s #5
2025-10-17 Se corrigió TODO el esquemaico
2025-10-17 Se corrigó el esquematico
2025-10-17 Se terminó de corregir el esquematico
2025-10-17 se cambio nombre al esquematico.s## a .sch
2025-10-17 se agrego el pcb de ejemplo
2025-10-22 se cambiaron componentes y se reviso que todo estuviera bien conectado
2025-10-22 esquematico actualizado
2025-10-28 Eliminar archivos PCB temporalmente
2025-10-28 Se organizaron los componentes en el PCB y se hicieron algunas uniones
2025-10-29 Se terminaron todas las uniones del PCB
2025-10-30 Se terminó todas las conexiones del PCB
2025-10-31 se creó un nuevo esquematico, circuito1.1
2025-10-31 se corrigieron lineas del pcb
2025-10-31 Se corrigio el PCB y algo en el esquematico
2025-11-02 Se terminó el PCB
2025-11-05 fix: revision pcb
2025-11-05 Se corrigió lo que el profesor indicó
2025-11-06 Se colocaron los nombres de los integrantes en la pcb
2025-11-06 se hizo un cambio
2025-11-07 ultima revision
2025-11-07 se hicieron correciones que nos dijo el profesor
